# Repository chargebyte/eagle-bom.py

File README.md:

eagle-bom.py
============

**This script is a replacement of the eagle ulp that creates a bom.**

It was initially written to fix a problem that eagle had with grouping parts with the same values but different attributes. The UPL did not make two BOM lines out of this scenario. This problem does not exist any more in eagle!

A side effect of using the ULP is that you do not need to have eagle on your machine that generates the releases.

The script is tested with python 2.7, 3.3

Installation
------------

This scripts requires cairocffi. On Debian distributions, there exists no pre-packaged
version of this python module, so you have to install the python development environment
and use pip to install this dependency:

### Linux

    $ apt-get install python-dev libffi-dev python-pip
    $ pip install cairocffi

### Windows

    $ pip install cffi
    $ pip install cairocffi
	
cairo / cairo-2 / cairo-gobject-2 dependencies can be solved by installing GTK+ from https://gtk-win.sourceforge.io/home/index.php/Main/Downloads followed by a restart of your machine.

You can use eagle-bom.py as follows:
------------------------------------

execute the script: "python eagle-bom.py"

this will give you a usage help as this:
usage: 
	mandatory arguments
	-c / --csv=		 csv where you want to store the BOM, may also be used for PDF output
	exclusive mandatory arguments (i.e. choose one of the following)
	-b / --brd=		 eagle board file that you want to use as input for the BOM
	-s / --sch=		 eagle schematic file that you want to use as input for the BOM
	
	optional arguments
	-h / --help		 print this help
	-v		 enable verbose output
	-t / --type=		 specify the type (valid types are value, part, sticker) of the output, default:part
	--variant=		 specify which variant should be used, default is to use the active variant as saved in the board file
	--separator=		 specify the separator that should be used as delimiter between each column in the output csv file, use 'TAB'to specify tabulator as separator
	--notestpads		 excludes all parts that have a attriute 'TP_SIGNAL_NAME' with a value
	--eagleversion		 print the version of eagle that was used to generate the board or schematic (only needs arguments for board or schematic, not for csv

	special attributes for EAGLE parts that are interpreted by this script:
		EXCLUDEFROMBOM		parts with this attribute set to a value other than blank will be excluded from the bom
		DO_NOT_PLACE		usually should have the value 'yes' for instructing the manufacturer to leave this part unplaced
		PROVIDED_BY		specify where the manufacturer gets the parts from
		additionally DNP markings from eagle variants are converted to use the DO_NOT_PLACE format

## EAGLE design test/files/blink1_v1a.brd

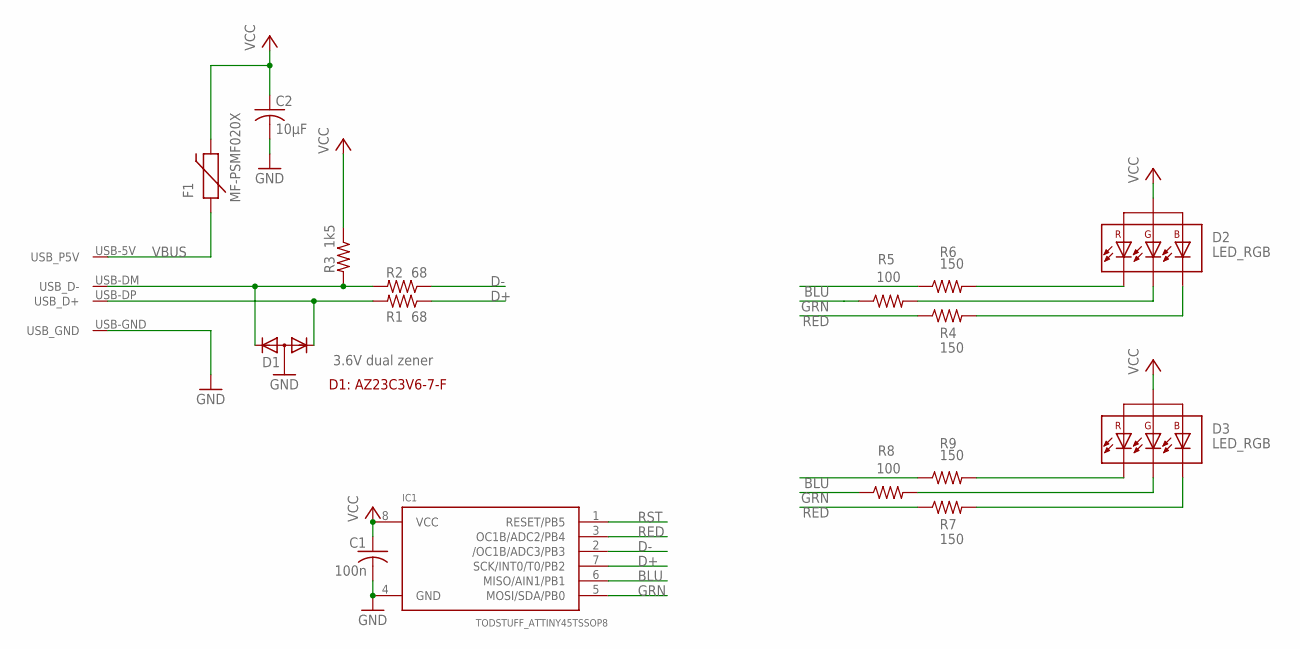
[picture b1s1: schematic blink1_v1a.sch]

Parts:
C1: 100n; C0402
C2: 10µF; C0603
D1: 3.6V dual zener; SOT23
D2, D3: LED_RGB; LED_1010
F1: MF-PSMF020X; 0805
IC1: TODSTUFF_ATTINY45TSSOP8; TSSOP8
R1, R2: 68; R0402
R3: 1k5; R0402
R4, R6, R7, R9: 150; R0402
R5, R8: 100; R0402
U$1: PCB-USB-DEV; PCB-USB-PAC

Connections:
BLU: IC1.6 (MISO/AIN1/PB1), R6.1, R9.1
D+: IC1.7 (SCK/INT0/T0/PB2), R1.1
D-: IC1.2 (/OC1B/ADC3/PB3), R2.1
GND: C1.2, C2.2, D1.3 (A), IC1.4 (GND), U$1.USB-GND (USB_GND)
GRN: IC1.5 (MOSI/SDA/PB0), R5.1, R8.1
unnamed: D1.1 (K1), R1.2, U$1.USB-DP (USB_D+)
unnamed: D1.2 (K2), R2.2, R3.2, U$1.USB-DM (USB_D-)
RBLU: D2.2 (C_R), R6.2
RBLU1: D3.2 (C_R), R9.2
RED: IC1.3 (OC1B/ADC2/PB4), R4.1, R7.1
RGRN: D2.4 (C_G), R5.2
RGRN1: D3.4 (C_G), R8.2
RRED: D2.3 (C_B), R4.2
RRED1: D3.3 (C_B), R7.2
RST: IC1.1 (RESET/PB5)
VBUS: F1.1, U$1.USB-5V (USB_P5V)
VCC: C1.1, C2.1, D2.1 (A), D3.1 (A), F1.2, IC1.8 (VCC), R3.1

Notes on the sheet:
D1: AZ23C3V6-7-F

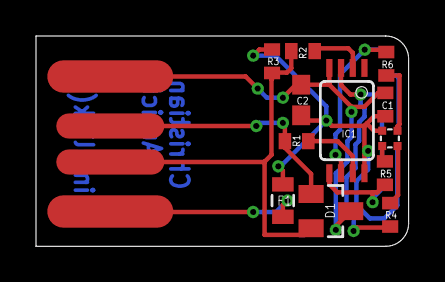
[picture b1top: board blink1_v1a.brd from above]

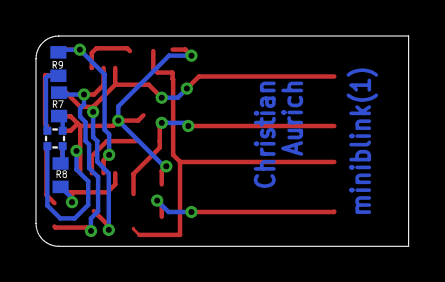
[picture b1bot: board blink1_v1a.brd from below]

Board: 2 copper layers, 20.7 x 11.7 mm, 17 parts (4 on the bottom side), 16 nets.

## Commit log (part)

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2013-01-16 fixed mistake in sort function that assumed numbers in the names of parts
    added text to the usage print
2013-01-24 changed name from i2se-bom to eagle-bom for publishing to github later
2013-01-24 added some descriptive text to the readme
2013-01-24 renamed project and formatting
2013-04-29 - fixed typo in README.md (upl->ulp) - changed print "blabla" syntax to print("blabla")
2013-04-29 fixed typo in usage -c was referenced twice, where it should have been -b once
2013-04-29 removed Qt based dialogs, tool is now fully command line based
2013-08-28 updated usage help
2013-09-25 added support for variants in eagle. This enables you to define variants which you can easily select to swap parts or define "do not populate" for parts. It also enables you to have different values 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
2013-09-25 updated README to have the information about the new variant feature in it
2014-02-02 added integration to travis-ci
2014-02-02 modifying travis settings file...
2014-02-02 updated travis CI rules and adopted eagle-bom.py to it
    adding more features to eagle-bom.py (i.e. it is now fully working with schematic files)
2014-02-02 adding some tests - blink1_v1a is a quick and dirty hardware project but will serve as a test project quite well
2014-02-02 fixing error discovered by https://travis-ci.org/I2SE/eagle-bom.py/jobs/18077759
2014-02-02 fixing error discovered by https://travis-ci.org/I2SE/eagle-bom.py/jobs/18077937
2014-02-02 removing more lines with syntax like: print "test" instead it should be print ("test")
2014-02-02 changed file open mode to improve compatibility over different python versions
2014-02-02 updated simple example files to use special characters (µ)
2014-02-02 fixed incompatibility to higher python versions - the strict use of types fell on my feet here...
2014-02-02 added two spaces of intend to lines 42 and 44 to keep lint happy
2014-02-02 changed code that extracts the description from the xml... eagle uses HTML within the description but strips it for BOMs
2014-02-02 adapting csv for sch > bom to new html stripping
2014-02-02 adopted README to new usage of the script
2014-02-19 if attribute EXCLUDE_FROM_BOM or DO_NOT_PLACE was set the tool crashed... this commit fixes that
2014-03-05 fixing error that no variants were used anymore... this was caused by the previous split into serveral functions where I forgot to return the selected variant name
2014-10-17 updating README for new parameter
2015-04-21 fixed problem that all but the columns with a fixed position were sorted kind of ugly (depending on the order they appeared in eagle xml file). Now the sorting should be alphabetically
2015-11-04 implementing DNP handling of eagle 7 for brd files fixing problem with default variants (if a board is saved with a selected variant this can be used for the BOM without selecting the variant explici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
2015-12-16 Looks like a bug introduced by a previous refactor that prevented selection of variant from working correctly.
2015-12-19 This commit contains a possible solution to the problem of pulling attributes from devices that contain multiple technologies.
2015-12-19 Added schematic with test case for parts that contain multiple technologies.
2015-12-21 Fixed bug that causes unicode character (specifically greek mu, 0xb5F) to not be written using the csv.DictWriter function. Hook tests will fail because code to extract technology attributes is cause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
2015-12-22 fixing minor syntax error
2015-12-22 fixing identation error that caused the function to be exited preliminary in some cases
2016-01-01 adding the possibility to extract the used eagle version to generate the passed schematic or board, fixes feature request #10
2016-01-01 adding help to the new version feature
2016-01-07 fixing issue that causes the script to fail: "deviseset" is not always present in the xml structure but the newly introduces feature in commit f459a8bdc4d04e5baf9d78bc565de96a6291b500 expects this at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
2016-01-07 fixing problem that was introduces by 9dae02a30ab88da2e2b79bd3bb6f994d0bc67414: iteritem is not available in python3. Since this new feature was to support python2 additionally to python3 I implement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
2016-01-13 improving sort function that is used for grouping of parts... the grouping should now be more stable and repeatable (this also should fix issue #4, which I now think was open until now)
2016-01-20 fixing most pylint "C" errors
2016-01-20 fixing indentation errors
2016-01-20 removing pylint warings that parens around print strings are superflous by importing the print function from __future__
2016-01-20 renaming column_sort_dict to columnSortDict for compatibility with pylint name conventions
2016-01-20 fixing previous commit which only TRIED to fix the naming issue for constant columnSortDict, which now is named COLUMNFIXEDORDER
2016-01-20 simplifying and splitting function bom_creation to satisfy pylint rules about max. number of local variables and number of branches inside a function
2016-01-20 reducing number of branches in bom_creation further by combining subsequent if statements and specifying Exception in more detail (using unicode codeword is a "SyntaxException" in python3) -
2016-01-20 "unicode" keyword generates NameError, not SyntaxError in python3 - changing exception accordingly
2016-01-20 updating pylint config to allow more branches in a function (this is the easiest way to allow the many branches to parse the command line options
2016-01-23 switching back to 12 branches in the pylint config
2016-01-23 disable warning for too many branches for the comman line parsing function locally
2016-01-23 changing syntax for pylint to locally disable the too-many-branches warning to "R0912" because this seems what the pylint in travis ci expects
2016-01-23 removing python version 2.6 from the travis test since we use features that are not compatible
2016-01-23 updating README: - removed outdated claim that eagle has a problem with different attributes from introduction - inserted travis build status - inserted supported python versions
2016-01-23 switching over to travis container based infrastructure
2016-01-23 adding deploy section to travis config file
2016-02-09 preparing version interface for CLI
2016-02-11 setting version as a fixed string
2016-02-11 fixing error that was introduced by commit #90041be that caused lines with only one part to have garbage in the 'NAME' field
2016-02-11 moving usage() and version() closer to the main() function
2016-02-11 making type argument easily extendable and check that it only takes valid arguments
2016-02-11 returning with error code if specified type is incorrect. This fixes issue #1
2016-02-11 adding more tests to the testsuite
2016-02-11 fixing some pylint errors
2016-02-19 implementing first working prototype of stickerbom
2016-02-22 fixing problem that pcb rendering is upside down due to the cairo coordinate system beeing different to the eagle coordinate system
2016-02-22 implementing of rotation for highlighting on stickers properly and reenabling zooming to the highlighted areas
2016-02-22 removing old todo and temporary code
2016-02-22 adding functionality to handle curved lines to the sticker export removing some old TODO stuff adding new TODO reminders
2016-02-22 adding LICENSE file
2016-02-23 adding feature to render circles in eagle footprints, this is needed for the stickerbom to see the orientation of most parts
2016-02-24 adding feature to the stickerbom export to not print sticker for parts that are either excluded from the BOM or that are marked as DNP
2016-02-24 refactoring for better code quality
2016-02-24 fixing syntax error (missing self argument for _rotate_point)
2016-02-26 fixing problem with last commit (I wanted to add "self" as argument but prepended it to the previously first argument
2016-02-26 moving to new style classes
2016-02-26 adding docstrings to all functions and classes
2016-02-26 replacing meaningless variable name "a" with "margin" what gives the variable the name that matches it's function
2016-02-26 giving meaningless variablenames x1/x2 and y1/y2 their true meaning with start_* and end_*
2016-02-26 changing variable names w and h for more meaningful alternatives width and height
2016-02-26 defining bounds, width and height in __init__ instead of in any other method
2016-02-26 replacing meaningless variable names by more meaningfull ones
2016-02-26 removing condition that checked for EXCLUDEFROMBOM here since these elements are already removed earlier
2016-02-26 making methods that do not use any class related informatin a static method
2016-02-26 disabling two pylint warnings that I think are not valid at all for this specific code
2016-02-26 allowing some more lines in script, arguments in function... this is just a temporary fix
2016-02-26 reducing complexity of some functions by reducing the number of local variables
2016-03-03 licensing the script under MIT after ACK of all participants was given
2016-03-03 adding cairo to the install requirements for travis
2016-03-03 moving from apt based installation of cairo to pip based installation
2016-03-04 in travis pylint does not work with the venv - therefore installing it via pip in the hope that this is able to find the used modules
2016-03-04 fixing problem introduced by recent refactoring that split up the code for reading in eagle files - it always used the BRD file, even if a SCH was passed
2016-03-04 fixing some more pylint problems that came up through the previous commit that installs pylint via pip
2016-03-04 fixing problem that was caused by recent refactoring (incorrectly parsing the XML tree)
2016-03-04 updating pylint config file for newer version of pylint
2016-03-04 making some minor adjustments in the code to satisfy pylint rules as well as "fixing" some problems in the pylint config, which should be fixed later
2016-03-05 fixing problem that between print and the opening bracket no space is allowed
2016-03-05 fixing issue #13
2016-03-05 solving pylint error
2016-03-05 renaming incorrectly written variable log_firmat to log_format
2016-03-05 updating usage()
2016-03-05 adding linebreak in too long line
2016-03-08 changing CLI to fix #11 and part of #17
2016-03-10 further improving the verbosity option adding debug output for stickerbom
2016-03-10 adding more debug output to sticker generation
2016-03-10 patching various problems: - feature stickerbom had an error in generating the correct coordinates for the labels - improving the log output (now printing to stderr to clear the output of the BOM to 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
2016-03-12 introducing tests for stdin/stdout support (#18)
2016-03-14 adding new test
2016-03-15 adding return value for default case
2016-03-16 adding proper way to get a temporary file to the testroutines that write an pdf for the stickerbom
2016-03-18 fixing problem with unicode characters... the solution now handles unicode characters for all types of bom outputs. (issue #22)
2016-03-18 changing tests to generate PDF #20
2016-03-27 fixing issue #23
2016-03-27 fixing issue #23 in an other way so that it does not break python 3.x support
2016-04-15 opening the pdf file with mode "wb" instead "w" fixes the problem that the current code did not work for python 3
2016-04-20 removing broken code that was there to compare the stickerBOM with a stored reference PDF... should add a better method to verify the output
2016-04-20 another try to get a consistent izip across different versions of python
2016-04-20 making it clear that the used izip might not be the builtin...
2016-04-20 removing support for python 3.2 (due to broken pylint and therefore bad testability)
2016-07-22 fixing issue #27 circles (commonly used to mark orientation of a part) were not placed correctly due to a incorrect mapping of the eagle to the cairo coordinate system
2016-07-22 bumping the version number to 0.2.1
2016-07-22 fixing pylint error (line too long)
2016-10-28 Add install hint
2016-10-28 Add shebang and mark file as executable
2016-12-18 as reported in issue #28 parts were mirrored when they were on bottom - this commit should resolve such problems. Root cause was that the parts were put in the correct place (by placing them where sa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
2016-12-18 fixing some problems with pylint
2016-12-18 fixing problem that "__SIDE" was written to CSV BOMs, which caused nosetests to fail
